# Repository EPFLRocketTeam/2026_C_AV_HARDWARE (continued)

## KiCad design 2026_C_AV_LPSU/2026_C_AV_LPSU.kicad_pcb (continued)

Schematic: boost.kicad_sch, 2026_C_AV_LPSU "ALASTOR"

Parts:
C13, C14, C15, C16: 4.7u 6.3V; C_0805_2012Metric
C17: 0.047u; C_0402_1005Metric
C18: 0.1u; C_0402_1005Metric
C20: 100p; C_0402_1005Metric
C21: 10p; C_0402_1005Metric
C22: 2.2u 6.3V; C_0603_1608Metric
C23: 6TPE150M; POSCAP_D12_D15_D15E_D2E_D2_D3L_D4; Mouser Part Number 667-6TPE150M
D5, D6, D7, D8: UPS5817E3_TR7; UPS5817E3TR7; Mouser Part Number 494-UPS5817E3/TR7
D12: RED; LED_0603_1608Metric
IC3: LTC3425EUH#PBF; QFN50P500X500X80-33N-D; Mouser Part Number 584-LTC3425EUH#PBF
L2, L3, L4, L5: XAL5030-222MEC; XAL5030222MEC; Mouser Part Number 994-XAL5030-222MEC
R17: 69.8k 1%; R_0402_1005Metric
R18: 15k 1%; R_0402_1005Metric
R19: 1k; R_0603_1608Metric
R20: 100k; R_0402_1005Metric
R21: 309k 1%; R_0402_1005Metric
R22: 100k 1%; R_0402_1005Metric
TP10: TestPoint; TestPoint_Pad_D1.5mm
TP11, TP12: TestPoint; TestPoint_THTPad_D1.5mm_Drill0.7mm

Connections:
/Project Architecture/Boost/COMP: C20.1, C21.1, IC3.13 (COMP)
/Project Architecture/Boost/FB: IC3.12 (FB), R21.2, R22.1, TP10.1
/Project Architecture/Boost/PGOOD: IC3.16 (PGOOD), R19.1, TP11.1
/Project Architecture/Boost/REFOUT: C18.1, IC3.15 (REFOUT)
/Project Architecture/Boost/SWA: D5.2 (A), IC3.3 (SWA), L2.2
/Project Architecture/Boost/SWB: D6.2 (A), IC3.6 (SWB), L3.2
/Project Architecture/Boost/SWC: D7.2 (A), IC3.19 (SWC), L4.2
/Project Architecture/Boost/SWD: D8.2 (A), IC3.22 (SWD), L5.2
/Project Architecture/Boost/VOUT: C13.1, C14.1, C15.1, C16.1, C23.1 (+), D5.1 (K), D6.1 (K), D7.1 (K), D8.1 (K), D12.2 (A), IC3.4 (VOUTA), IC3.5 (VOUTB), IC3.10 (VOUTS), IC3.14 (BURST), IC3.20 (VOUTC), IC3.21 (VOUTD), R21.1, TP12.1; also elsewhere on the board
/Project Architecture/CHRG_OUT: C22.1, IC3.29 (VIN), IC3.31 (~SHDN), L2.1, L3.1, L4.1, L5.1; also elsewhere on the board
GND: C13.2, C14.2, C15.2, C16.2, C17.1, C18.2, C21.2, C22.2, C23.2 (-), IC3.1 (GNDA), IC3.2 (GNDA_1), IC3.7 (GNDB), IC3.8 (GNDB_1), IC3.9 (REFEN), IC3.11 (SGND), IC3.17 (GNDC), IC3.18 (GNDC_1), IC3.23 (GNDD), IC3.24 (GNDD_1), IC3.26 (CCM), IC3.30 (SYNCIN), IC3.33 (GND_(EP)), R17.2, R18.2, R20.2, R22.2; also elsewhere on the board
unnamed: C20.2, R20.1
unnamed: D12.1 (K), R19.2
unnamed: IC3.27 (ILIM), R17.1
unnamed: IC3.28 (RT), R18.1
unnamed: C17.2, IC3.32 (SS)

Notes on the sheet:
4-Phase Boost converter
Configuration: f_OSC = 4MHz -> Rt = 15k VOUT = 5V -> Rfb1 = 309k, Rfb2 = 100k

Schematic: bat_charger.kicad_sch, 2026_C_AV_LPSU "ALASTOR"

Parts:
C1: 10p; C_0603_1608Metric
C2: 270p; C_0603_1608Metric
C3: 1u 50V 1206; C_1206_3216Metric
C4: 0.33u; C_0603_1608Metric
C5: 22u 50V; CP_Elec_6.3x5.7
C6: 0.47u 16V; C_0402_1005Metric
C7, C8: 4.7u 6.3V; C_0603_1608Metric
C9: 22u 6.3V 1206; C_1206_3216Metric
D1: DFLS240-7; POWERDI123; Mouser Part Number 621-DFLS240-7
D2: GREEN; LED_0603_1608Metric
D3: RED; LED_0603_1608Metric
D14: SBRT5A50SAF-13; SODFL5226X110N; Mouser Part Number 621-SBRT5A50SAF-13
F1: Polyfuse; 2016L26024MR
IC1: LTC4090EDJC#PBF; LTC4089EDJC5TRPBF; Mouser Part Number 584-LTC4090EDJC#PBF
J3: Conn_01x02_Pin; TerminalBlock_Phoenix_PT-1,5-2-3.5-H_1x02_P3.50mm_Horizontal
L1: XAL4030-682MEC; XFL4030472MEB; Mouser Part Number 994-XAL4030-682MEC
R1: 13.2k 1%; R_0603_1608Metric
R2: 1.97k 1%; R_0603_1608Metric
R3: 10k 1% NTC; R_0603_1608Metric
R4, R5: 40.2k 1%; R_0603_1608Metric
R6: 59k 1%; R_0603_1608Metric
R7: 422 1%; R_0603_1608Metric
R8: 1k 1%; R_0402_1005Metric
R9: 1; R_0603_1608Metric
R10, R11: 680; R_0603_1608Metric
TP3, TP4, TP6, TP7: TestPoint; TestPoint_THTPad_D1.5mm_Drill0.7mm
U1, U2: SI2333DS-T1-E3; TO-236_VIS

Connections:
/Project Architecture/Battery Charger/*CHRG: IC1.8 (~CHRG), R10.2, TP6.1
/Project Architecture/Battery Charger/*HVPR: IC1.7 (~HVPR), R8.1, R11.2, TP7.1, U2.1 (G)
/Project Architecture/Battery Charger/BAT: C8.1, IC1.11 (BAT), U1.3 (D); also elsewhere on the board
/Project Architecture/Battery Charger/BOOST: C6.1, IC1.19 (BOOST)
/Project Architecture/Battery Charger/GATE: IC1.10 (GATE), U1.1 (G)
/Project Architecture/Battery Charger/HVIN: C3.1, C5.1, D14.1 (K), IC1.21 (HVIN), IC1.22 (HVEN), TP3.1; also elsewhere on the board
/Project Architecture/Battery Charger/HVIN_EXT: F1.1, J3.1
/Project Architecture/Battery Charger/HVOUT: C9.1, D3.2 (A), IC1.18 (HVOUT), L1.2, U2.3 (D)
/Project Architecture/Battery Charger/NTC: IC1.5 (NTC), R1.2, R2.1
/Project Architecture/Battery Charger/PROG: IC1.9 (PROG), R5.2
/Project Architecture/Battery Charger/RT: IC1.3 (RT), R4.2
/Project Architecture/Battery Charger/SW: C6.2, D1.2 (K), IC1.20 (SW), L1.1
/Project Architecture/Battery Charger/VC: C1.1, C2.1, IC1.4 (VC)
/Project Architecture/Battery Charger/VNTC: IC1.6 (VNTC), R1.1
/Project Architecture/CHRG_OUT: C7.1, D2.2 (A), IC1.13 (OUT), R8.2, TP4.1, U1.2 (S), U2.2 (S); also elsewhere on the board
GND: C1.2, C3.2, C4.2, C5.2, C7.2, C9.2, D1.1 (A), IC1.1 (SYNC), IC1.16 (SUSP), IC1.23 (EP_1), IC1.24 (EP_2), IC1.25 (EP_3), J3.2, R3.2, R4.1, R5.1, R6.2, R7.2, R9.2; also elsewhere on the board
unnamed: C2.2, R6.1
unnamed: C8.2, R9.1
unnamed: D2.1 (K), R10.1
unnamed: D3.1 (K), R11.1
unnamed: D14.2 (A), F1.2
unnamed: IC1.14 (CLPROG), R7.1
unnamed: C4.1, IC1.17 (TIMER)
unnamed: R2.2, R3.1

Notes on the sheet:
HVIN ORing EXT: 24Vmax
Battery charger with PowerPath control Inputs (by priority): 6V-36V DC, 3.7V Li-ion battery HVOUT/OUT: VBAT+0.3V if DC adapter present, else VBAT
https://www.vishay.com/docs/33011/convtabs.pdf
NTC config: Charge temp. thresholds -5°C to +55°C rCOLD = 1.97k, rHOT = 13.2k
Configuration: f_OSC = 800kHz -> Rt = 40.2k I_IN,MAX = 2.4A -> R_CLPROG = 422 I_CHG = 1.2A -> R_PROG = 40.2k tTIMER = 4h -> C_TIMER = 0.33uF

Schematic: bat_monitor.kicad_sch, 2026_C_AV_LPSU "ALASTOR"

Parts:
BT1: 1049; BAT_1049; PARTREV F
C10: 0.1u; C_0603_1608Metric
C11: 0.47u; C_0603_1608Metric
C29: 22n; C_0603_1608Metric
C30: 3.3n; C_0603_1608Metric
C32: 10TPB47M; POSCAP_B1_B1S_B1G_B15G_B2_B2S; Mouser Part Number 667-10TPB47M
D9: 1N4148WT; D_SOD-523
D10: GREEN; LED_0603_1608Metric
D11: RED; LED_0603_1608Metric
IC5: LTC4368IMS-1#PBF; SOP50P490X110-10N; Mouser Part Number 584-LTC4368IMS1PBF
Q1: FDS9926A; SOIC-8_3.9x4.9mm_P1.27mm
R12: 0.042; R_1206_3216Metric
R13, R14: 10; R_0603_1608Metric
R26: 0.017; R_1206_3216Metric
R27: 1.2M 1%; R_0603_1608Metric
R28: 163k 1%; R_0603_1608Metric
R29: 136k 1%; R_0603_1608Metric
R30: 1k; R_0603_1608Metric
R31: 22k; R_0603_1608Metric
S1, S3: CJS-1200TB; B-TYPE; Mouser Part Number 229-CJS-1200TB
TP1, TP5: TestPoint; TestPoint_THTPad_D1.5mm_Drill0.7mm
TP2: TestPoint; TestPoint_Pad_D1.5mm
TP13: TestPoint; TestPoint_Pad_D1.0mm
U3: INA228; VSSOP-10_3x3mm_P0.5mm

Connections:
+3V3: C10.1, U3.6 (VS); also elsewhere on the board
/Project Architecture/Battery Charger/BAT: R12.1, R14.2, TP2.1; also elsewhere on the board
/Project Architecture/Battery/*FAULT: D11.1 (K), IC5.7 (~FAULT), TP1.1
/Project Architecture/Battery/*SHDN: IC5.6 (~SHDN), S1.2, TP13.1
/Project Architecture/Battery/A1: S3.2, U3.1 (A1)
/Project Architecture/Battery/BAT_MON_VBUS: C32.1 (+), IC5.8 (VOUT), R12.2, R13.2, R26.1, U3.8 (Vbus)
/Project Architecture/Battery/BAT_P+: BT1.P1, BT1.P2, IC5.1 (VIN), Q1.5 (D2), Q1.6 (D2), R27.1, R30.1, S1.3, TP5.1
/Project Architecture/Battery/GATE: IC5.10 (GATE), Q1.2 (G1), Q1.4 (G2), R31.2
/Project Architecture/Battery/OV: IC5.3 (OV), R28.2, R29.1
/Project Architecture/Battery/SENSE: IC5.9 (SENSE), Q1.7 (D1), Q1.8 (D1), R26.2
/Project Architecture/Battery/UV: IC5.2 (UV), R27.2, R28.1
GND: BT1.N1, BT1.N2, C10.2, C29.2, C30.1, C32.2 (-), D10.1 (K), IC5.5 (GND), R29.2, S1.1, S3.1, U3.2 (A0), U3.7 (GND); also elsewhere on the board
unnamed: C30.2, R31.1
unnamed: D9.2 (A), R30.2
unnamed: D9.1 (K), D10.2 (A), D11.2 (A)
unnamed: C29.1, IC5.4 (RETRY)
unnamed: Q1.1 (S1), Q1.3 (S2)
unnamed: C11.2, R13.1, U3.10 (Vin+)
unnamed: C11.1, R14.1, U3.9 (Vin-)
SCL: U3.5 (SCL); also elsewhere on the board
SDA: S3.3, U3.4 (SDA); also elsewhere on the board

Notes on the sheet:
0603L200SL-V: I_hold = 2A (1.45A at 60°C) I_trip = 4A (1s)
Address selection
0x40
Configuration: UV: 2.5V OV: 5.5V Offset: 3mV -> R3 = 1.2M, R1 = 136k, R2 = 163k OC: 3A -> R_SENSE = 17m
0x48
R_shunt = V_SHUNT_MAX / I_MAX I_MAX = 4A R_shunt = 42mOhm
Battery/Circuit Protection Controller - Reverse polarity - Overvoltage/Undervoltage - Overcurrent

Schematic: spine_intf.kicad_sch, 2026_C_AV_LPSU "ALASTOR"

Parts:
C12: 2u2; C_0603_1608Metric
C19, C24: 1u; C_0603_1608Metric
D4: PESD4USB3UTBS-QX; PESD4USB3UTBSQX; Manufacturer_Part_Number PESD4USB3UTBS-QX
D13: BLUE; LED_0603_1608Metric
IC2: LT3960EMSE#PBF; SOP50P490X110-11N; Mouser Part Number 584-LT3960EMSE#PBF
IC4: TPS7A0533PDBZR; SOT95P237X112-3N; Mouser Part Number 595-TPS7A0533PDBZR
J1: DIN41612_02x16_AB; DIN41612_B2_2x16_Male_Horizontal_THT
J2: Conn_01x03_Pin; PinHeader_1x03_P2.54mm_Vertical_SMD_Pin1Right
R15, R16: 4k7; R_0603_1608Metric
R32: 1k; R_0603_1608Metric
TP8, TP9: TestPoint; TestPoint_THTPad_D1.5mm_Drill0.7mm

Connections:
+3V3: C12.1, C24.1, IC2.6 (VIN), IC2.8 (VCC), IC4.2 (OUT), R15.1, R16.1, TP9.1; also elsewhere on the board
+5V: C19.1, IC4.3 (IN), J1.a14, J1.b14, R32.1, TP8.1; also elsewhere on the board
/Project Architecture/Battery Charger/HVIN_SPINE: J1.a15, J1.a16, J1.b15, J1.b16; also elsewhere on the board
/Project Architecture/Spine Interface/I2C_MON_SCLH: D4.4 (CH3), D4.7 (N.C._2), IC2.4 (CANSCLH), J1.a12
/Project Architecture/Spine Interface/I2C_MON_SCLL: D4.5 (CH4), D4.6 (N.C._1), IC2.5 (CANSCLL), J1.b12
/Project Architecture/Spine Interface/I2C_MON_SDAH: D4.2 (CH2), D4.9 (N.C._3), IC2.2 (CANSDAH), J1.a11
/Project Architecture/Spine Interface/I2C_MON_SDAL: D4.1 (CH1), D4.10 (N.C._4), IC2.1 (CANSDAL), J1.b11
GND: C12.2, C19.2, C24.2, D4.3 (GND_1), D4.8 (GND_2), D13.1 (K), IC2.3 (GND_1), IC2.11 (GND_2), IC4.1 (GND), J1.a9, J1.a13, J1.b9, J1.b13, J2.1; also elsewhere on the board
unnamed: D13.2 (A), R32.2
SCL: IC2.9 (SCL), J2.2, R16.2; also elsewhere on the board
SDA: IC2.10 (SDA), J2.3, R15.2; also elsewhere on the board

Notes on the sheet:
I2C-CAN transceiver
5V-3V3 200mA LDO

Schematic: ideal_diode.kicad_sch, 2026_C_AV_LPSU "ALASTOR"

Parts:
C25, C26: 22u; C_0603_1608Metric
Q3: PSMN6R4-30MLDX; PSMN6R430MLDX; Mouser Part Number 771-PSMN6R4-30MLDX
U6: LTC4357DCB; SON50P300X200X80-7N-D

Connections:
/Project Architecture/Boost/Ideal Diode/D_OUT: C25.1, C26.1, Q3.5 (D_1), Q3.6 (D_2), Q3.7 (D_3), Q3.8 (D_4), Q3.9 (D_5), Q3.10 (D_6), Q3.11 (D_7), U6.1 (OUT), U6.6 (Vdd); also elsewhere on the board
/Project Architecture/Boost/VOUT: Q3.1 (S_1), Q3.2 (S_2), Q3.3 (S_3), U6.2 (IN); also elsewhere on the board
GND: C25.2, C26.2, U6.4 (GND), U6.7 (PAD); also elsewhere on the board
unnamed: Q3.4 (G), U6.3 (GATE)

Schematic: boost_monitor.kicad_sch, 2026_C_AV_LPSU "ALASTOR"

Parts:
C27: 0.47u; C_0603_1608Metric
C28: 0.1u; C_0603_1608Metric
R23, R25: 10; R_0603_1608Metric
R24: 0.021; R_0805_2012Metric
S2: CJS-1200TB; B-TYPE; Mouser Part Number 229-CJS-1200TB
U4: INA228; VSSOP-10_3x3mm_P0.5mm

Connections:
+3V3: C28.1, U4.2 (A0), U4.6 (VS); also elsewhere on the board
+5V: R23.2, R24.1; also elsewhere on the board
/Project Architecture/Boost/Ideal Diode/D_OUT: R24.2, R25.2, U4.8 (Vbus); also elsewhere on the board
/Project Architecture/Boost/Monitor/A1: S2.2, U4.1 (A1)
GND: C28.2, S2.1, U4.7 (GND); also elsewhere on the board
unnamed: C27.2, R25.1, U4.10 (Vin+)
unnamed: C27.1, R23.1, U4.9 (Vin-)
SCL: U4.5 (SCL); also elsewhere on the board
SDA: S2.3, U4.4 (SDA); also elsewhere on the board

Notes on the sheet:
Address selection
0x41
0x49
R_shunt = V_SHUNT_MAX / I_MAX V_SHUNT_MAX = 163.8mV I_MAX = 2A R_shunt = 21mOhm

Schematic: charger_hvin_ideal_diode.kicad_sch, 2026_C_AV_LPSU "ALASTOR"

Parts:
Q2: FDMC86102LZ; FDMC86139P; Mouser Part Number 512-FDMC86102LZ
U5: LTC4357DCB; SON50P300X200X80-7N-D

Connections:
/Project Architecture/Battery Charger/HVIN: Q2.5 (D_1), Q2.6 (D_2), Q2.7 (D_3), Q2.8 (D_4), Q2.9, U5.1 (OUT), U5.6 (Vdd); also elsewhere on the board
/Project Architecture/Battery Charger/HVIN_SPINE: Q2.1 (S_1), Q2.2 (S_2), Q2.3 (S_3), U5.2 (IN); also elsewhere on the board
GND: U5.4 (GND), U5.7 (PAD); also elsewhere on the board
unnamed: Q2.4 (G), U5.3 (GATE)

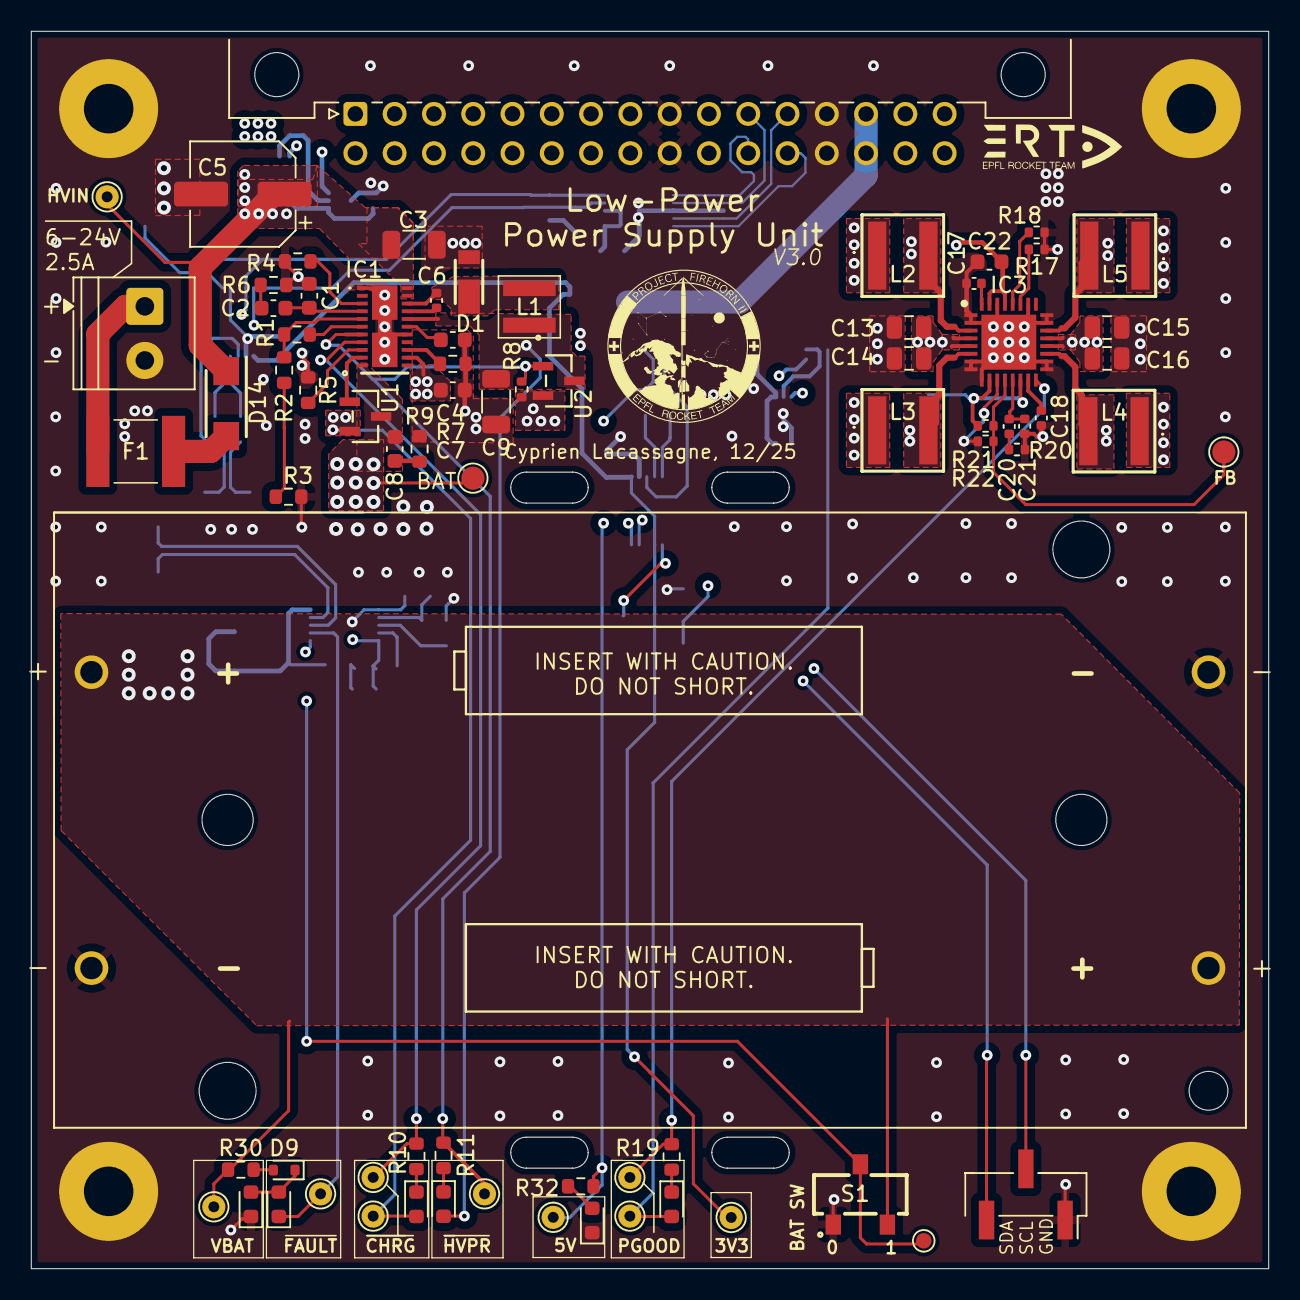
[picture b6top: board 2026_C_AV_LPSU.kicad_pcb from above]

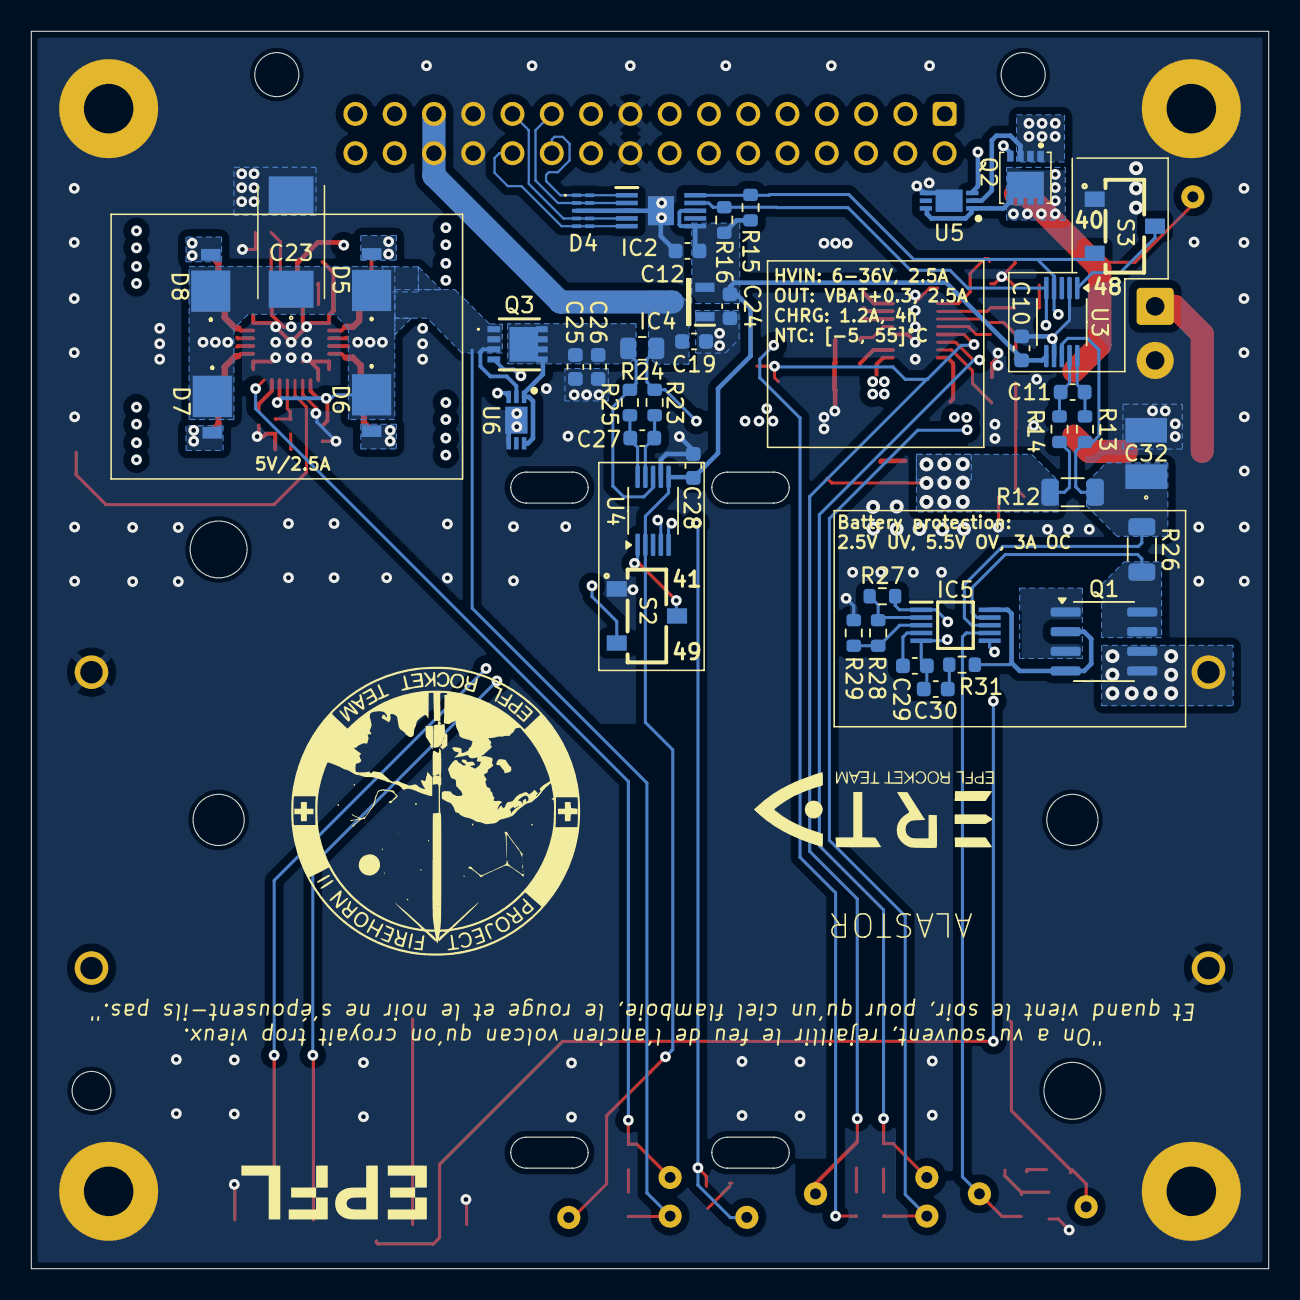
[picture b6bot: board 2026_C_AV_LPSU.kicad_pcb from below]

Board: 4 copper layers, 80.0 x 80.0 mm, 117 parts (43 on the bottom side), 70 nets.

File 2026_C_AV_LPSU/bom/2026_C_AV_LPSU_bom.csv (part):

"Reference","Value","Footprint","Datasheet","Qty","Closest STD","Manufacturer_Part_Number","Maximum Value","Mfr","Mfr. ID","Minimum Value","Mouser Part Number","Ratings","Tolerance"
"BT1","1049","Battery_holder:BAT_1049","","1","","","","","","","","",""
"C1,C21","10p","Capacitor_SMD:C_0402_1005Metric,Capacitor_SMD:C_0603_1608Metric","~","2","","","","","","","","",""
"C2","270p","Capacitor_SMD:C_0603_1608Metric","~","1","","","","","","","","",""
"C3","1u 50V 1206","Capacitor_SMD:C_1206_3216Metric","~","1","","","","","","","","",""
"C4","0.33u","Capacitor_SMD:C_0603_1608Metric","~","1","","","","","","","","",""
"C5","22u 50V","Capacitor_SMD:CP_Elec_6.3x5.7","~","1","","","","","","","","",""
"C6","0.47u 16V","Capacitor_SMD:C_0402_1005Metric","~","1","","","","","","","","",""
"C7,C8,C13,C14,C15,C16","4.7u 6.3V","Capacitor_SMD:C_0603_1608Metric,Capacitor_SMD:C_0805_2012Metric","~","6","","","","","","","","",""
"C9","22u 6.3V 1206","Capacitor_SMD:C_1206_3216Metric","~","1","","","","","","","","",""
"C10,C18,C28","0.1u","Capacitor_SMD:C_0402_1005Metric,Capacitor_SMD:C_0603_1608Metric","~","3","","","","","","","","",""
"C11,C27","0.47u","Capacitor_SMD:C_0603_1608Metric","~","2","","","","","","","","",""
"C12","2u2","Capacitor_SMD:C_0603_1608Metric","~","1","","","","","","","","",""
"C17","0.047u","Capacitor_SMD:C_0402_1005Metric","~","1","","","","","","","","",""
"C19,C24","1u","Capacitor_SMD:C_0603_1608Metric","~","2","","","","","","","","",""
"C20","100p","Capacitor_SMD:C_0402_1005Metric","~","1","","","","","","","","",""
"C22","2.2u 6.3V","Capacitor_SMD:C_0603_1608Metric","~","1","","","","","","","","",""
"C23","6TPE150M","6TPE150M:POSCAP_D12_D15_D15E_D2E_D2_D3L_D4","https://componentsearchengine.com/Datasheets/1/6TPE150M.pdf","1","","6TPE150M","","","","","667-6TPE150M","",""
"C25,C26","22u","Capacitor_SMD:C_0603_1608Metric","187-CL21A226MAYNNNE","2","","","","","","","","",""
"C29","22n","Capacitor_SMD:C_0603_1608Metric","~","1","","","","","","","","",""
"C30","3.3n","Capacitor_SMD:C_0603_1608Metric","~","1","","","","","","","","",""
"C32","10TPB47M","10TPB47M:POSCAP_B1_B1S_B1G_B15G_B2_B2S","http://industrial.panasonic.com/cdbs/www-data/pdf/AAA8000/AA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","1","","10TPB47M","","","","","667-10TPB47M","",""
"D1","DFLS240-7","DFLS240-7:POWERDI123","https://componentsearchengine.com/Datasheets/1/DFLS240-7.pdf","1","","DFLS240-7","","","","","621-DFLS240-7","",""
"D2,D10","GREEN","LED_SMD:LED_0603_1608Metric","~","2","","","","","","","","",""
"D3,D11,D12","RED","LED_SMD:LED_0603_1608Metric","~","3","","","","","","","","",""
"D4","PESD4USB3UTBS-QX","PESD4USB3UTBS-QX:PESD4USB3UTBSQX","https://www.digikey.ph/en/products/detail/nexperia-usa-inc/P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","1","","PESD4USB3UTBS-QX","","","","","","",""
"D5,D6,D7,D8","UPS5817E3_TR7","UPS5817E3_TR7:UPS5817E3TR7","https://www.arrow.com/en/products/ups5817e3tr7/microchip-tec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","4","","UPS5817E3/TR7","","","","","494-UPS5817E3/TR7","",""
"D9","1N4148WT","Diode_SMD:D_SOD-523","https://www.diodes.com/assets/Datasheets/ds30396.pdf","1","","","","","","","","",""
"D13","BLUE","LED_SMD:LED_0603_1608Metric","~","1","","","","","","","","",""
"D14","SBRT5A50SAF-13","SBRT5A50SAF-13:SODFL5226X110N","https://www.diodes.com/assets/Datasheets/SBRT5A50SAF.pdf","1","","SBRT5A50SAF-13","","","","","621-SBRT5A50SAF-13","",""
"F1","Polyfuse","2016L260_24MR:2016L26024MR","~","1","","","","","","","","",""
"IC1","LTC4090EDJC#PBF","LTC4090EDJC#PBF:LTC4089EDJC5TRPBF","https://www.analog.com/LTC4090-3/datasheet","1","","LTC4090EDJC#PBF","","","","","584-LTC4090EDJC#PBF","",""
"IC2","LT3960EMSE#PBF","LT3960EMSE#PBF:SOP50P490X110-11N","https://www.analog.com/LT3960/datasheet","1","","LT3960EMSE#PBF","","","","","584-LT3960EMSE#PBF","",""
"IC3","LTC3425EUH#PBF","LTC3425EUH#PBF:QFN50P500X500X80-33N-D","https://datasheet.datasheetarchive.com/originals/distributor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","1","","LTC3425EUH#PBF","","","","","584-LTC3425EUH#PBF","",""
"IC4","TPS7A0533PDBZR","TPS7A0533PDBZR:SOT95P237X112-3N","https://www.ti.com/lit/gpn/TPS7A05","1","","TPS7A0533PDBZR","","","","","595-TPS7A0533PDBZR","",""
"IC5","LTC4368IMS-1#PBF","LTC4368IMS-1#PBF:SOP50P490X110-10N","https://www.analog.com/media/en/technical-documentation/data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","1","","LTC4368IMS-1#PBF","","","","","584-LTC4368IMS1PBF","",""
"J1","DIN41612_02x16_AB","Connector_DIN:DIN41612_B2_2x16_Male_Horizontal_THT","~","1","","","","","","","","",""
"J2","Conn_01x03_Pin","Connector_PinHeader_2.54mm:PinHeader_1x03_P2.54mm_Vertical_SMD_Pin1Right","~","1","","","","","","","","",""
"J3","Conn_01x02_Pin","TerminalBlock_Phoenix:TerminalBlock_Phoenix_PT-1,5-2-3.5-H_1x02_P3.50mm_Horizontal","~","1","","","","","","","","",""
"L1","XAL4030-682MEC","XAL4030-682MEC:XFL4030472MEB","https://www.coilcraft.com/pdfs/xal4000.pdf","1","","XAL4030-682MEC","","","","","994-XAL4030-682MEC","",""
"L2,L3,L4,L5","XAL5030-222MEC","XAL5030-222MEC:XAL5030222MEC","https://www.coilcraft.com/getmedia/49bc46c8-4b2c-45b9-9b6c-2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","4","","XAL5030-222MEC","","","","","994-XAL5030-222MEC","",""
"Q1","FDS9926A","Package_SO:SOIC-8_3.9x4.9mm_P1.27mm","https://www.onsemi.com/pub/Collateral/FDS9926A-D.pdf","1","","","","","","","","",""
"Q2","FDMC86102LZ","FDMC86102LZ:FDMC86139P","https://www.onsemi.com/pub/Collateral/FDMC86102LZ-D.PDF","1","","FDMC86102LZ","","","","","512-FDMC86102LZ","",""
"Q3","PSMN6R4-30MLDX","PSMN6R4-30MLDX:PSMN6R430MLDX","https://assets.nexperia.com/documents/data-sheet/PSMN6R4-30MLD.pdf","1","","PSMN6R4-30MLDX","","","","","771-PSMN6R4-30MLDX","",""
"R1","13.2k 1%","Resistor_SMD:R_0603_1608Metric","~","1","","","","","","","","",""
"R2","1.97k 1%","Resistor_SMD:R_0603_1608Metric","~","1","","","","","","","","",""
"R3","10k 1% NTC","Resistor_SMD:R_0603_1608Metric","~","1","","","","","","","","",""
"R4,R5","40.2k 1%","Resistor_SMD:R_0603_1608Metric","~","2","","","","","","","","",""
"R6","59k 1%","Resistor_SMD:R_0603_1608Metric","~","1","","","","","","","","",""
"R7","422 1%","Resistor_SMD:R_0603_1608Metric","~","1","","","","","","","","",""
"R8","1k 1%","Resistor_SMD:R_0402_1005Metric","~","1","","","","","","","","",""
"R9","1","Resistor_SMD:R_0603_1608Metric","~","1","","","","","","","","",""
"R10,R11","680","Resistor_SMD:R_0603_1608Metric","~","2","","","","","","","","",""
"R12","0.042","Resistor_SMD:R_1206_3216Metric","~","1","","","","","","","","",""
"R13,R14,R23,R25","10","Resistor_SMD:R_0603_1608Metric","~","4","","","","","","","","",""
"R15,R16","4k7","Resistor_SMD:R_0603_1608Metric","~","2","","","","","","","","",""
"R17","69.8k 1%","Resistor_SMD:R_0402_1005Metric","~","1","","","","","","","","",""
"R18","15k 1%","Resistor_SMD:R_0402_1005Metric","~","1","","","","","","","","",""
"R19,R30,R32","1k","Resistor_SMD:R_0603_1608Metric","~","3","","","","","","","","",""
"R20","100k","Resistor_SMD:R_0402_1005Metric","~","1","","","","","","","","",""
"R21","309k 1%","Resistor_SMD:R_0402_1005Metric","~","1","","","","","","","","",""
"R22","100k 1%","Resistor_SMD:R_0402_1005Metric","~","1","","","","","","","","",""
"R24","0.021","Resistor_SMD:R_0805_2012Metric","~","1","","","","","","","","",""
"R26","0.017","Resistor_SMD:R_1206_3216Metric","~","1","","","","","","","","",""
"R27","1.2M 1%","Resistor_SMD:R_0603_1608Metric","~","1","","","","","","","","",""
"R28","163k 1%","Resistor_SMD:R_0603_1608Metric","~","1","","","","","","","","",""
"R29","136k 1%","Resistor_SMD:R_0603_1608Metric","~","1","","","","","","","","",""
"R31","22k","Resistor_SMD:R_0603_1608Metric","~","1","","","","","","","","",""
"S1,S2,S3","CJS-1200TB","CJS-1200TB:B-TYPE","http://www.nidec-copal-electronics.com/e/catalog/switch/cjs.pdf","3","","CJS-1200TB","","","","","229-CJS-1200TB","",""
"TP1,TP2,TP3,TP4,TP5,TP6,TP7,TP8,TP9,TP10,TP11,TP12,TP13","TestPoint","TestPoint:TestPoint_Pad_D1.0mm,TestPoint:TestPoint_Pad_D1.5mm,TestPoint:TestPoint_THTPad_D1.5mm_Drill0.7mm","~","13","","","","","","","","",""
"U1,U2","SI2333DS-T1-E3","SI2333DS_T1_E3:TO-236_VIS","SI2333DS-T1-E3","2","","","","","","","","",""
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
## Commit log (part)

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2025-12-13 2026_C_AV_LPSU-v3.0
2025-12-16 Squashed '2026_C_AV_SPINE/' content from commit 1a14b8c
    git-subtree-dir: 2026_C_AV_SPINE
    git-subtree-split: 1a14b8cf8c2f1335ccb24668576e28eeefbff93a
2026-02-03 LPSU & TMB
2026-02-03 TMB .step
2026-02-05 TMB: changed SMA ref
2026-02-05 LPSU: 04-02 backup
2026-02-17 added SPINE
2026-02-17 add PC/FDR/FC
2026-02-17 DRC OK SPINE
2026-02-18 FC FIX: DIN41612 was not centered
2026-02-18 documentation FDR
2026-02-27 spine almost finished
2026-02-27 Layout spine finished
2026-03-05 updates: FC & SPINE
